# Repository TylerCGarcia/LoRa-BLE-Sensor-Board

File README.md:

# LoRa_BLE_Sensor Board
CAD: KiCad 9.0
# Overview
A RAK4630 based sensor board that uses BLE and LoRaWAN. This board is configured to use three industrial sensors simultaneously. 

Sensor 1 and Sensor 2 are designed so the sensor can be powered with 3.3V, 5V, 12V or 24V that are switched between through firmware. Sensor 3 has the options for 3.3V or 5V. It is designed for each sensor to have its own unique 
power supply, independent of the other sensor. Sensor 1 and Sensor 2 are designed for work with either digital or analog sensors. Sensor 3 is deisned for digital sensors with 3.3V logic level or to control up to two relays.

# Schematic Breakdown
**RAK4630** 
 - A combination module of an nRF52840 and SX1262
   * The nRF52840 has a cortex M4 and uses BLE
   * The SX1262 is a SPI controlled LoRa chip
 - There is an SWD connector for programming
 - There are two buttons
   * SW1 is connected to the reset pin on the nRF52840
   * SW2 is connected to P0.09

**NPM1300** 
 - Power management for the board
   * Programmable over I2C with the RAK4630
 - Used to charge the battery and works as a fuel guage
 - Contains two buck converters
   * Buck 1 is used for Sensor 3 3.3V output
   * Buck 2 is used at 3.3V to supply Vdd for the entire board
 - Contains 2 LDOs
   * Used if either Sensor 1 or Sensor 2 are set to 3.3V
 - Switch SW3
   * Used to change power modes on npm1300 or to do a power cycle of the board
 - RGB LED
   * Used for charging/error status of the npm1300 and as an led controlled by RAK4630

**Boost 1** 
 - TLV61046ADBVR Boost Converter
   * Up to 28V output with load disconnect
   * Output is determined by resistors in feedback
 - NMOS mosfets
   * Allow for feedback reistances to be changes to adjust output
   * BOOST1_FB_CTRL1 set to 0, BOOST1_FB_CTRL2 set to 0 --> 24V
   * BOOST1_FB_CTRL1 set to 1, BOOST1_FB_CTRL2 set to 0 --> 12V
   * BOOST1_FB_CTRL1 set to 0, BOOST1_FB_CTRL2 set to 1 --> 6V
   * BOOST1_FB_CTRL1 set to 1, BOOST1_FB_CTRL2 set to 1 --> 5V

**Boost 2** 
 - TLV61046ADBVR Boost Converter
   * Up to 28V output with load disconnect
   * Output is determined by resistors in feedback
 - NMOS mosfets
   * Allow for feedback reistances to be changes to adjust output
   * BOOST2_FB_CTRL1 set to 0, BOOST2_FB_CTRL2 set to 0 --> 24V
   * BOOST2_FB_CTRL1 set to 1, BOOST2_FB_CTRL2 set to 0 --> 12V
   * BOOST2_FB_CTRL1 set to 0, BOOST2_FB_CTRL2 set to 1 --> 6V
   * BOOST2_FB_CTRL1 set to 1, BOOST2_FB_CTRL2 set to 1 --> 5V

**Boost 3** 
 - TLV61046ADBVR Boost Converter
   * Up to 28V output with load disconnect
   * Output is determined by resistors in feedback
 - This boost has one configuration which is 5V

**Sensor 3 ESD**
 - ESD protection for Sensor 3 power and digital lines
  * ESD is for 5V for power and 3.3V for input lines

**Power Switches** 
 - Connects boost and ldo/buck outputs so only 1 is used by the sensor
   * Boost outputs have priority if both are enabled
 - ESD protection for sensor power
   * Designed for 24V for Sensor 1 and Sensor 2
   
**Digital Inputs** 
 - MOSFET based level shifters
   * Allows sensor digital logic to be translated from sensor power to Vdd
 - ESD protection for digital inputs
   * Designed for 24V for Sensor 1 and Sensor 2

**Analog Inputs** 
 - 5 inputs meant for external sensors
   * 2 designed for 4-20mA current sensors
   * 2 designed to read voltages up to 28V
   * 3 designed for feedback to the voltage of the sensor power

**USB** 
 - 6 pin jst PH connector to use with external USB-C connector
 - ESD protection for data lines and USB power

**Interface** 
 - Three screw terminal connectors for the sensors
   * Designed for pluggaple screw terminals
 
**Debug**
 - Two JST SH connectors for interfacing with Button 1 and nRF Reset
 - Two 2.54mm pin header for debugging Sensor 1 and Sensor 2

# Power Analysis

# Bugs/To-Do
- Add fuses to sensor power outputs

# Revision History
Current Version: **V1.1**

Version Breakdown: `[Major Chanegs]`.`[Minor Changes]`

### V1.1
- Changed level shifters for sensor to have isolation from output
- Removed 18650 battery connectors and NTC
  * Replaced with 3 pin JST PH and JST SH for external battery
- Removed on board relay
- Added Sensor 3 connectors
 * Can be configured for digital sensors with 3.3V or 5V output
 * Output is either 5V from boost converter or Buck 1 of npm1300
 * This connector can be used for an external relay
- Added 2 pin JST SH connectors to have Button 1 and nRF Reset pins be external if desired
- Added connector for NFC antenna
- Changed mounting holes from M3 to M2

### V1.0
- Initial Design of Board

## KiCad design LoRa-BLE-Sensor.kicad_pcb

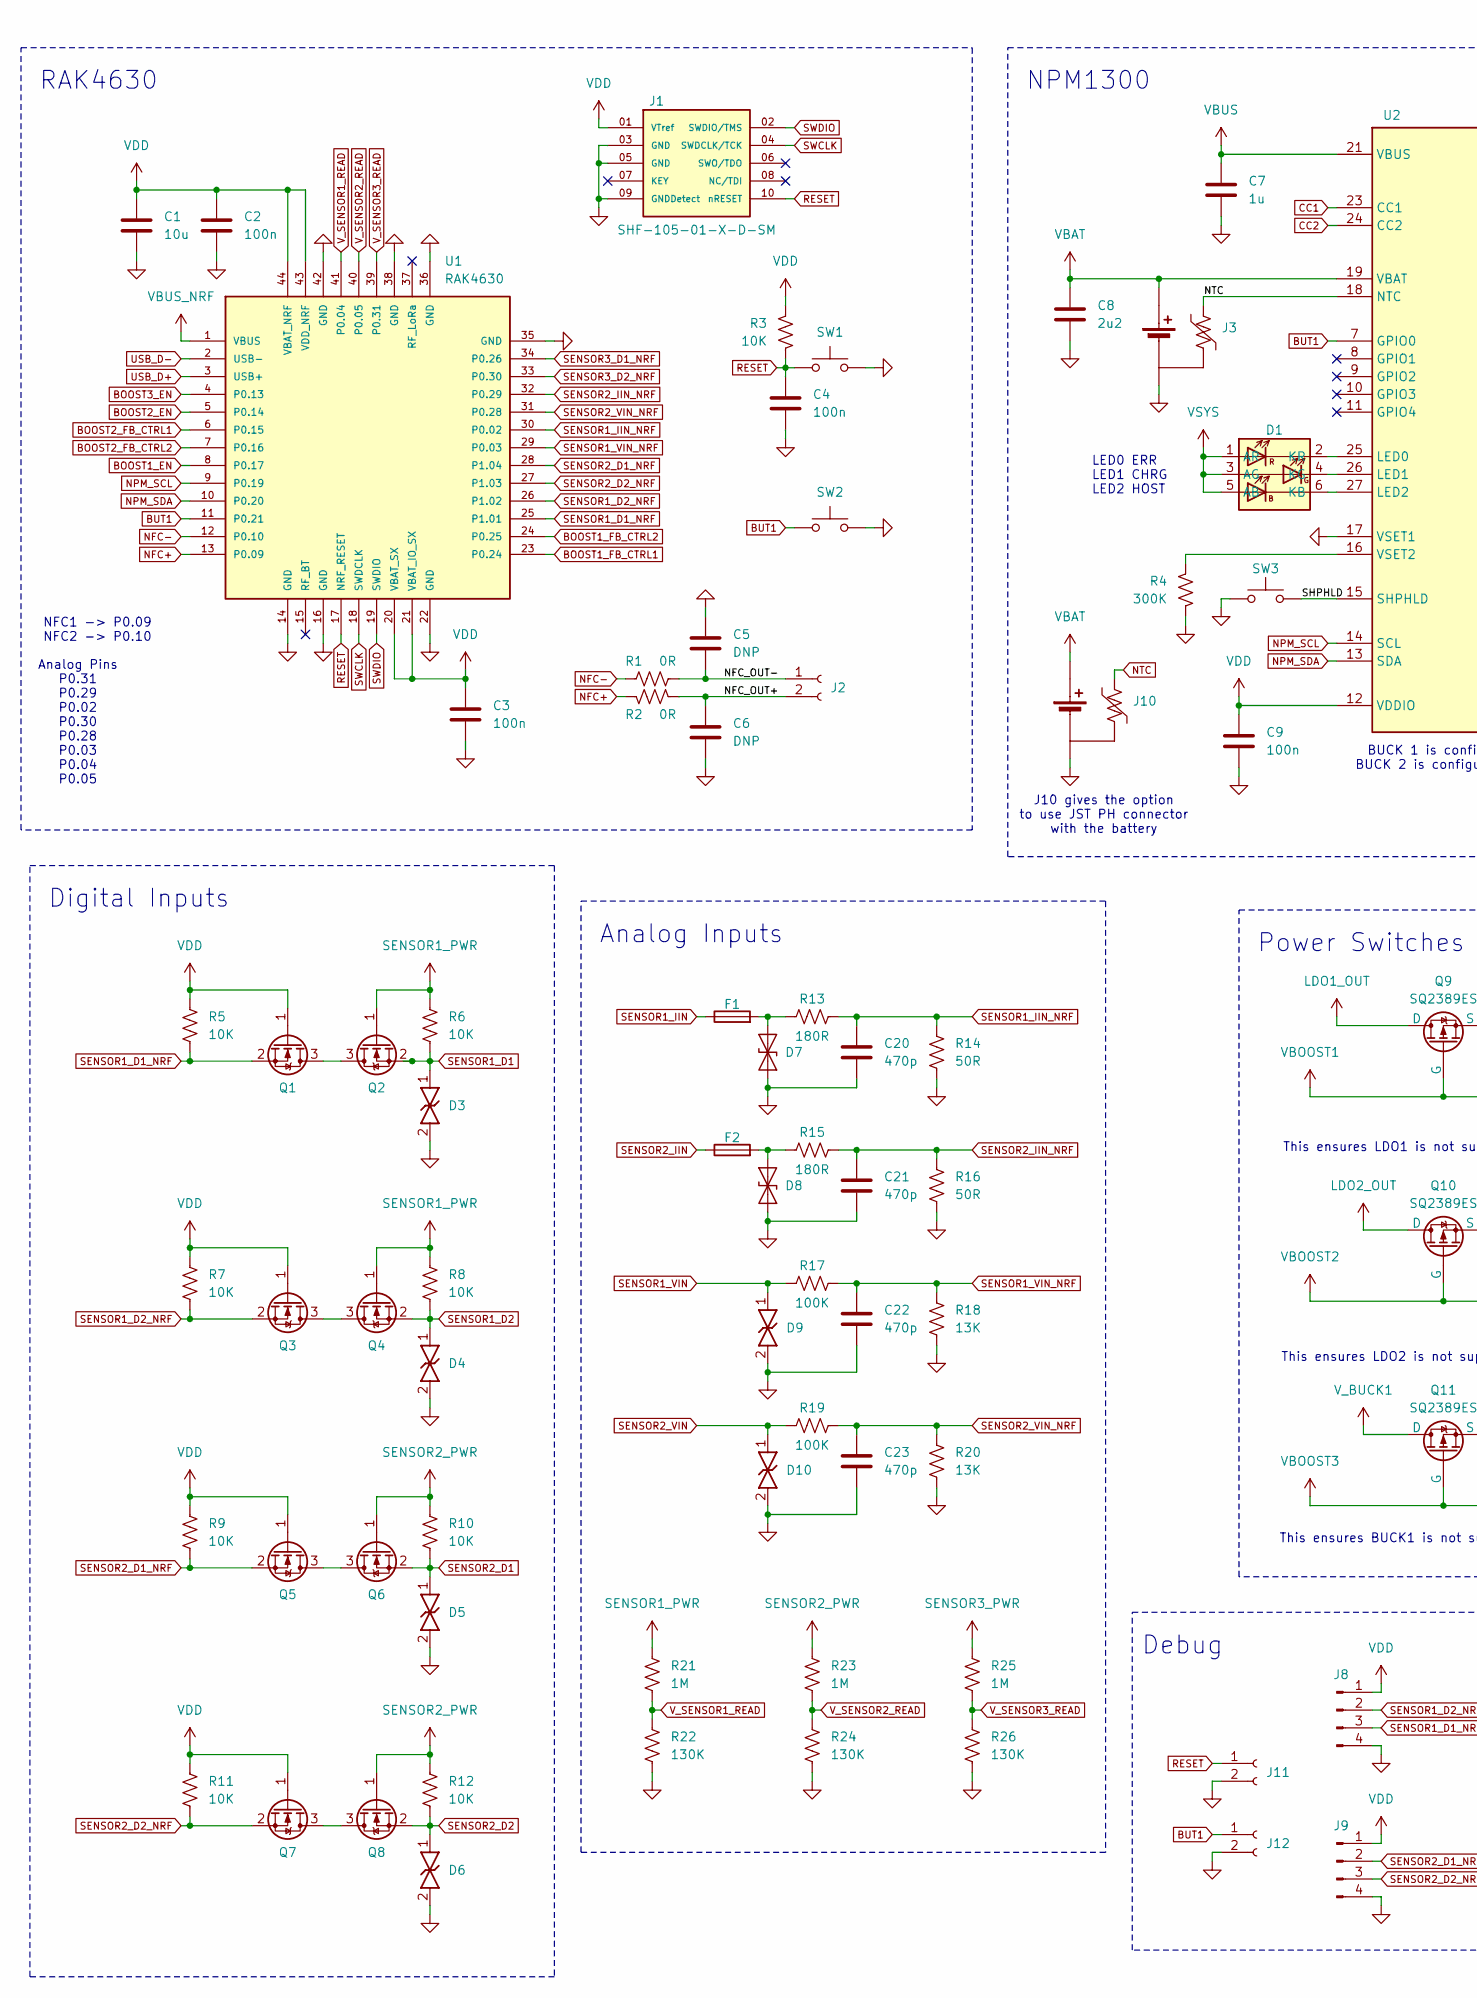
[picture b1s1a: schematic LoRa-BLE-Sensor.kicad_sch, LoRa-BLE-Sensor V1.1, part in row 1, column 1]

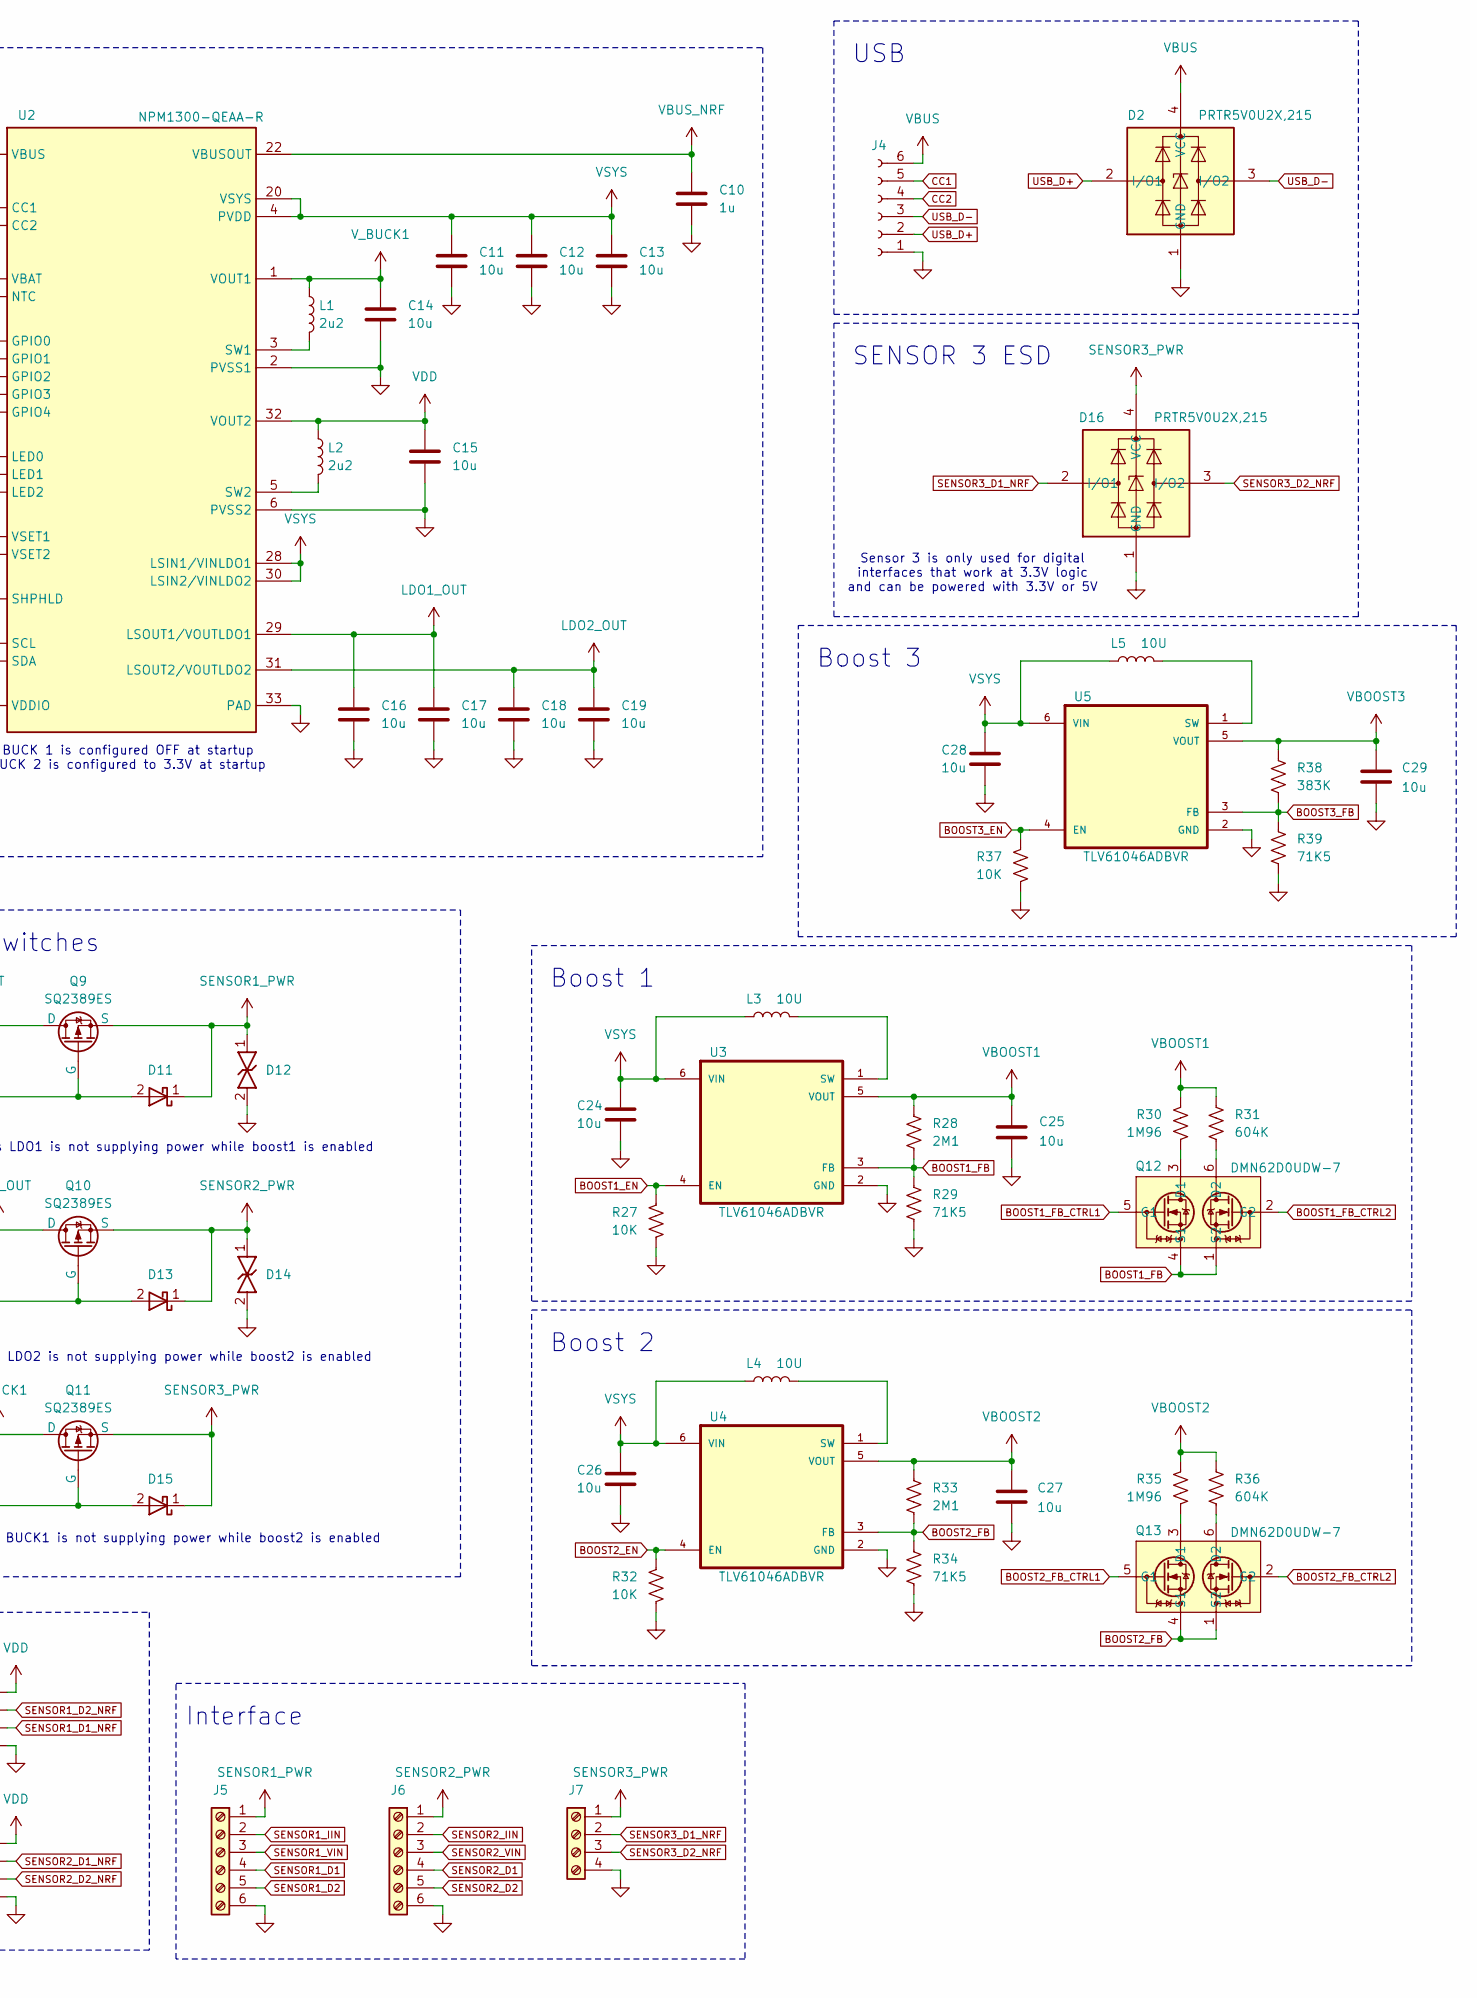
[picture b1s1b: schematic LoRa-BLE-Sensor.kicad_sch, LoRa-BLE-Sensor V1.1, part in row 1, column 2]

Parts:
C1, C11, C12, C13, C14, C15, C16, C17, C18, C19, C24, C26, C28: 10u; C_0603_1608Metric
C2, C3, C4, C9: 100n; C_0402_1005Metric
C5, C6: DNP; C_0402_1005Metric
C7, C10: 1u; C_0402_1005Metric
C8: 2u2; C_0402_1005Metric
C20, C21, C22, C23: 470p; C_0402_1005Metric
C25, C27, C29: 10u; C_0805_2012Metric
D1: ASMB-TTF0-0A20B; ASMBTTF00A20B; Mouser Part Number 630-ASMB-TTF0-0A20B
D2, D16: PRTR5V0U2X,215; PRTR5V0U2X
D3, D4, D5, D6, D9, D10, D12, D14: UDD32C24L01; SOD2612X120N
D7, D8: SMAJ10CA; D_SMA
D11, D13, D15: BAT54W-HG3-08; SOD3716X135N
F1, F2: MF-USMF005-2; Fuse_1210_3225Metric
J1: SHF-105-01-X-D-SM; SAMTEC_SHF-105-01-X-D-SM
J2: Conn_01x02_Socket; JST_ACH_BM02B-ACHSS-GAN-ETF_1x02-1MP_P1.20mm_Vertical
J3: Battery_with_NTC; JST_SH_BM03B-SRSS-TB_1x03-1MP_P1.00mm_Vertical
J4: Conn_01x06_Socket; JST_6PIN_PH_VERTICAL_SMD
J5, J6: Screw_Terminal_01x06; PhoenixContact_MCV_1,5_6-G-3.81_1x06_P3.81mm_Vertical
J7: Screw_Terminal_01x04; PhoenixContact_MCV_1,5_4-G-3.81_1x04_P3.81mm_Vertical
J8, J9: Conn_01x04_Pin; PinHeader_1x04_P2.54mm_Vertical
J10: Battery_with_NTC; JST_3PIN_PH_Vertical
J11, J12: Conn_01x02_Socket; JST_SH_2-PIN_Vertical
L1, L2: 2u2; L_0805_2012Metric
L3, L4, L5: 10U; L_1008_2520Metric
Q1, Q2, Q3, Q4, Q5, Q6, Q7, Q8: DMN67D7L; SOT-23
Q9, Q10, Q11: SQ2389ES; SOT-23-3
Q12, Q13: DMN62D0UDW-7; SOT65P222X110-6N; Mouser Part Number 621-DMN62D0UDW-7
R1, R2: 0R; L_0402_1005Metric
R3, R5, R6, R7, R8, R9, R10, R11, R12, R27, R32, R37: 10K; R_0402_1005Metric
R4: 300K; R_0402_1005Metric
R13, R15: 180R; R_0805_2012Metric
R14, R16: 50R; L_0402_1005Metric
R17, R19: 100K; R_0402_1005Metric
R18, R20: 13K; R_0402_1005Metric
R21, R23, R25: 1M; R_0402_1005Metric
R22, R24, R26: 130K; R_0402_1005Metric
R28, R33: 2M1; R_0402_1005Metric
R29, R34, R39: 71K5; R_0402_1005Metric
R30, R35: 1M96; R_0402_1005Metric
R31, R36: 604K; R_0402_1005Metric
R38: 383K; R_0402_1005Metric
SW1, SW2, SW3: SW_Push; PTS815SJM250SMTRLFS_2Pin
U1: RAK4630
U2: NPM1300-QEAA-R; QFN50P500X500X90-33N
U3, U4, U5: TLV61046ADBVR; SOT95P280X145-6N

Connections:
/NFC_OUT+: C6.1, J2.2, R2.2
/NFC_OUT-: C5.1, J2.1, R1.2
/SHPHLD: SW3.2, U2.15 (SHPHLD)
BOOST1_EN: R27.1, U1.8 (P0.17), U3.4 (EN)
BOOST1_FB: Q12.1 (S2), Q12.4 (S1), R28.2, R29.1, U3.3 (FB)
BOOST1_FB_CTRL1: Q12.5 (G1), U1.23 (P0.24)
BOOST1_FB_CTRL2: Q12.2 (G2), U1.24 (P0.25)
BOOST2_EN: R32.1, U1.5 (P0.14), U4.4 (EN)
BOOST2_FB: Q13.1 (S2), Q13.4 (S1), R33.2, R34.1, U4.3 (FB)
BOOST2_FB_CTRL1: Q13.5 (G1), U1.6 (P0.15)
BOOST2_FB_CTRL2: Q13.2 (G2), U1.7 (P0.16)
BOOST3_EN: R37.1, U1.4 (P0.13), U5.4 (EN)
BOOST3_FB: R38.2, R39.1, U5.3 (FB)
BUT1: J12.1, SW2.1, U1.11 (P0.21), U2.7 (GPIO0)
CC1: J4.5, U2.23 (CC1)
CC2: J4.4, U2.24 (CC2)
GND: C1.2, C2.2, C3.2, C4.2, C5.2, C6.2, C7.2, C8.2, C9.2, C10.2, C11.2, C12.2, C13.2, C14.2, C15.2, C16.2, C17.2, C18.2, C19.2, C20.2, C21.2, C22.2, C23.2, C24.2, C25.2, C26.2, C27.2, C28.2, C29.2, D2.1 (GND), D3.2, D4.2, D5.2, D6.2, D7.2 (A2), D8.2 (A2), D9.2, D10.2, D12.2, D14.2, D16.1 (GND), J1.03 (GND), J1.05 (GND), J1.09 (GNDDetect), J3.1 (-), J4.1, J5.6, J6.6, J7.4, J8.4, J9.4, J10.1 (-), J11.2, J12.2, R4.2, R14.2, R16.2, R18.2, R20.2, R22.2, R24.2, R26.2, R27.2, R29.2, R32.2, R34.2, R37.2, R39.2, SW1.2, SW2.2, SW3.1, U1.14 (GND), U1.16 (GND), U1.22 (GND), U1.35 (GND), U1.36 (GND), U1.38 (GND), U1.42 (GND), U2.2 (PVSS1), U2.6 (PVSS2), U2.17 (VSET1), U2.33 (PAD), U3.2 (GND), U4.2 (GND), U5.2 (GND)
LDO1_OUT: C16.1, C17.1, Q9.3 (D), U2.29 (LSOUT1/VOUTLDO1)
LDO2_OUT: C18.1, C19.1, Q10.3 (D), U2.31 (LSOUT2/VOUTLDO2)
NFC+: R2.1, U1.13 (P0.09)
NFC-: R1.1, U1.12 (P0.10)
NPM_SCL: U1.9 (P0.19), U2.14 (SCL)
NPM_SDA: U1.10 (P0.20), U2.13 (SDA)
NTC: J3.2 (NTC), J10.2 (NTC), U2.18 (NTC)
unnamed: D1.6 (KB), U2.27 (LED2)
unnamed: D1.4 (KG), U2.26 (LED1)
unnamed: D1.2 (KR), U2.25 (LED0)
unnamed: D7.1 (A1), F1.2, R13.1
unnamed: D8.1 (A1), F2.2, R15.1
unnamed: Q1.3 (D), Q2.3 (D)
unnamed: Q3.3 (D), Q4.3 (D)
unnamed: Q5.3 (D), Q6.3 (D)
unnamed: Q7.3 (D), Q8.3 (D)
unnamed: Q12.3 (D1), R30.2
unnamed: Q12.6 (D2), R31.2
unnamed: Q13.3 (D1), R35.2
unnamed: Q13.6 (D2), R36.2
unnamed: L1.2, U2.3 (SW1)
unnamed: L2.2, U2.5 (SW2)
unnamed: R4.1, U2.16 (VSET2)
unnamed: L3.2, U3.1 (SW)
unnamed: L4.2, U4.1 (SW)
unnamed: L5.2, U5.1 (SW)
RESET: C4.1, J1.10 (nRESET), J11.1, R3.2, SW1.1, U1.17 (NRF_RESET)
SENSOR1_D1: D3.1, J5.4, Q2.2 (S), R6.2
SENSOR1_D1_NRF: J8.3, Q1.2 (S), R5.2, U1.25 (P1.01)
SENSOR1_D2: D4.1, J5.5, Q4.2 (S), R8.2
SENSOR1_D2_NRF: J8.2, Q3.2 (S), R7.2, U1.26 (P1.02)
SENSOR1_IIN: F1.1, J5.2
SENSOR1_IIN_NRF: C20.1, R13.2, R14.1, U1.30 (P0.02)
SENSOR1_PWR: D11.1 (K), D12.1, J5.1, Q2.1 (G), Q4.1 (G), Q9.2 (S), R6.1, R8.1, R21.1
SENSOR1_VIN: D9.1, J5.3, R17.1
SENSOR1_VIN_NRF: C22.1, R17.2, R18.1, U1.29 (P0.03)
SENSOR2_D1: D5.1, J6.4, Q6.2 (S), R10.2
SENSOR2_D1_NRF: J9.2, Q5.2 (S), R9.2, U1.28 (P1.04)
SENSOR2_D2: D6.1, J6.5, Q8.2 (S), R12.2
SENSOR2_D2_NRF: J9.3, Q7.2 (S), R11.2, U1.27 (P1.03)
SENSOR2_IIN: F2.1, J6.2
SENSOR2_IIN_NRF: C21.1, R15.2, R16.1, U1.32 (P0.29)
SENSOR2_PWR: D13.1 (K), D14.1, J6.1, Q6.1 (G), Q8.1 (G), Q10.2 (S), R10.1, R12.1, R23.1
SENSOR2_VIN: D10.1, J6.3, R19.1
SENSOR2_VIN_NRF: C23.1, R19.2, R20.1, U1.31 (P0.28)
SENSOR3_D1_NRF: D16.2 (I/O1), J7.2, U1.34 (P0.26)
SENSOR3_D2_NRF: D16.3 (I/O2), J7.3, U1.33 (P0.30)
SENSOR3_PWR: D15.1 (K), D16.4 (VCC), J7.1, Q11.2 (S), R25.1
SWCLK: J1.04 (SWDCLK/TCK), U1.18 (SWDCLK)
SWDIO: J1.02 (SWDIO/TMS), U1.19 (SWDIO)
USB_D+: D2.2 (I/O1), J4.2, U1.3 (USB+)
USB_D-: D2.3 (I/O2), J4.3, U1.2 (USB-)
VBAT: C8.1, J3.3 (+), J10.3 (+), U2.19 (VBAT)
VBOOST1: C25.1, D11.2 (A), Q9.1 (G), R28.1, R30.1, R31.1, U3.5 (VOUT)
VBOOST2: C27.1, D13.2 (A), Q10.1 (G), R33.1, R35.1, R36.1, U4.5 (VOUT)
VBOOST3: C29.1, D15.2 (A), Q11.1 (G), R38.1, U5.5 (VOUT)
VBUS: C7.1, D2.4 (VCC), J4.6, U2.21 (VBUS)
VBUS_NRF: C10.1, U1.1 (VBUS), U2.22 (VBUSOUT)
VDD: C1.1, C2.1, C3.1, C9.1, C15.1, J1.01 (VTref), J8.1, J9.1, L2.1, Q1.1 (G), Q3.1 (G), Q5.1 (G), Q7.1 (G), R3.1, R5.1, R7.1, R9.1, R11.1, U1.20 (VBAT_SX), U1.21 (VBAT_IO_SX), U1.43 (VDD_NRF), U1.44 (VBAT_NRF), U2.12 (VDDIO), U2.32 (VOUT2)
VSYS: C11.1, C12.1, C13.1, C24.1, C26.1, C28.1, D1.1 (AR), D1.3 (AG), D1.5 (AB), L3.1, L4.1, L5.1, U2.4 (PVDD), U2.20 (VSYS), U2.28 (LSIN1/VINLDO1), U2.30 (LSIN2/VINLDO2), U3.6 (VIN), U4.6 (VIN), U5.6 (VIN)
V_BUCK1: C14.1, L1.1, Q11.3 (D), U2.1 (VOUT1)
V_SENSOR1_READ: R21.2, R22.1, U1.41 (P0.04)
V_SENSOR2_READ: R23.2, R24.1, U1.40 (P0.05)
V_SENSOR3_READ: R25.2, R26.1, U1.39 (P0.31)

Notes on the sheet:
Analog Pins P0.31 P0.29 P0.02 P0.30 P0.28 P0.03 P0.04 P0.05
Sensor 3 is only used for digital interfaces that work at 3.3V logic and can be powered with 3.3V or 5V
BUCK 1 is configured OFF at startup BUCK 2 is configured to 3.3V at startup
NPM1300
Boost 1
Debug
LED0 ERR LED1 CHRG LED2 HOST
RAK4630
This ensures LDO1 is not supplying power while boost1 is enabled
NFC1 -> P0.09 NFC2 -> P0.10
This ensures BUCK1 is not supplying power while boost2 is enabled
Digital Inputs
This ensures LDO2 is not supplying power while boost2 is enabled
J10 gives the option to use JST PH connector with the battery
USB
Boost 3
Power Switches
Interface
Analog Inputs
SENSOR 3 ESD
Boost 2

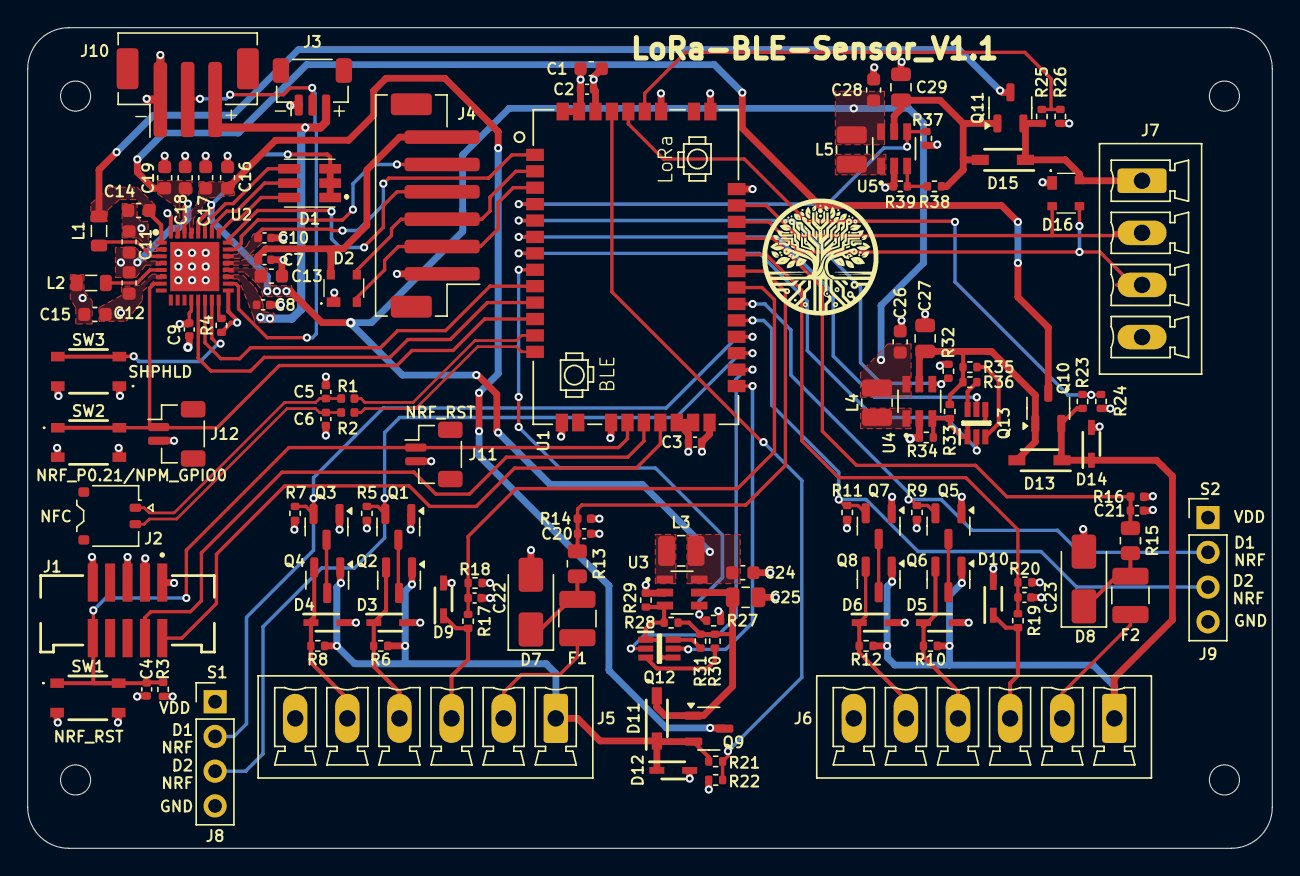
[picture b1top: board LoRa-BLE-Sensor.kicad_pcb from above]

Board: 4 copper layers, 91.0 x 60.0 mm, 124 parts (0 on the bottom side), 81 nets.

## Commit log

2025-03-06 Schematic + JPEG
2025-03-06 File Naming
2025-03-06 updated schematic
2025-03-12 placement file
2025-03-12 rearranged files
2025-05-21 beginning V1.1 deisgn
2025-05-22 renaming pin labels
2025-05-22 removed power switch voltage dividers
2025-05-22 added sensor 3
2025-05-23 sensor3 schematic almost done
2025-05-23 Beginning routing V1.1
2025-05-23 labels fixed
2025-05-23 signal routing
2025-05-23 NFC antenna route + connector
2025-05-23 mounting holes + routing
2025-05-24 all tracks routed and DRC passed
2025-05-24 finished renaming and routing
2025-05-27 replaced battery connectors
2025-05-27 switching branches
2025-05-27 rearranged board down to 60mm
2025-05-27 external battery design finished
2025-05-27 schematic update
2025-05-27 user drawings
2025-05-27 switch branches
2025-05-27 pre-merge
2025-05-27 external battery merged to main
2025-05-27 shortened width by 5mm
2025-05-29 added docs and manufacturing V1.1
2025-05-29 added logo to front
2025-05-29 added pdf to schematic
2025-05-29 manufacturing update
2025-05-29 Changed BOM name
2025-05-29 Update REAMDE
